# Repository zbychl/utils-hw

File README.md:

# utils-hw
Hardware utilities projects

## stlink-v2-clone-to-cortex-dbg-etm-adapter
Project for simple adapter allowing to attach STLink v2 Clone to the
20-Pin Cortex Debug + ETM Connector for ARM MCUs.

### STLink v2 clone
> **WARNING**: Be careful, there is a two different STLink v2 clone pinout version: http://blog.linuxbits.io/wp-content/uploads/2016/02/P1160461_clipped.jpg

This adapter is supports the following pinout

|          |            |
|----------|------------|
| RST  - 1 | 2  - SWCLK |
| GND  - 3 | 4  - SWDIO |
| SWIM - 5 | 6  - GND   |
| 3.3V - 7 | 8  - 3.3V  |
| 5.0V - 9 | 10 - 5.0V  |

### ARM MCU JTAG
http://www2.keil.com/coresight/coresight-connectors/

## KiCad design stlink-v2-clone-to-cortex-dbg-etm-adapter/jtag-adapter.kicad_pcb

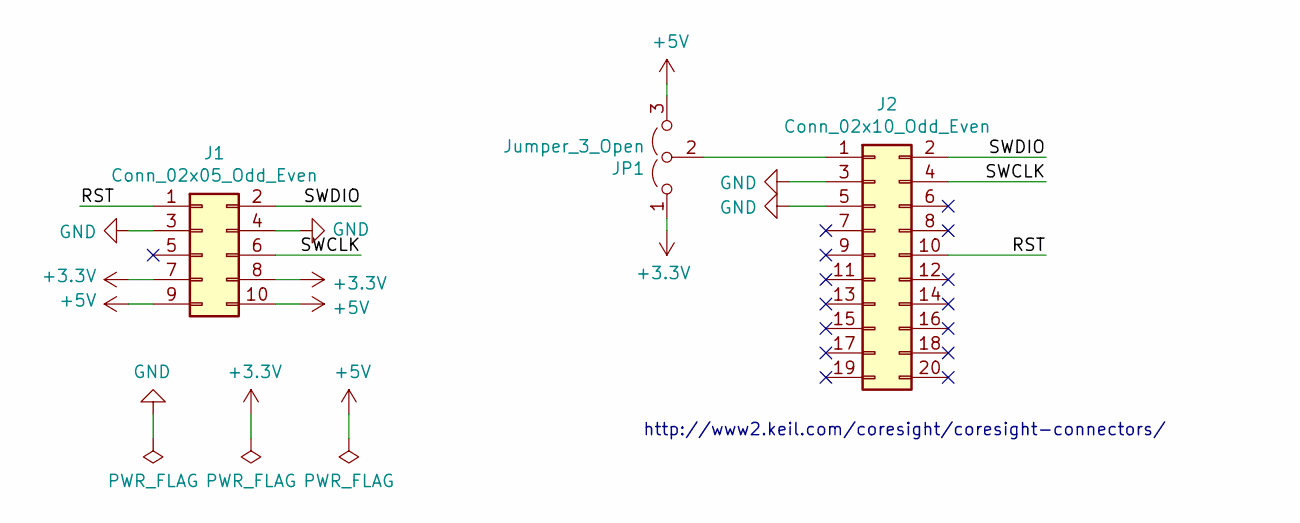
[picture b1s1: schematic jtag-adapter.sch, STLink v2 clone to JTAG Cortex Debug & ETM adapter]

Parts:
J1: Conn_02x05_Odd_Even; PinHeader_2x05_P2.54mm_Vertical_SMD
J2: Conn_02x10_Odd_Even; PinSocket_2x10_P1.27mm_Vertical_SMD
JP1: Jumper_3_Open; PinHeader_1x03_P1.27mm_Vertical

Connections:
+3V3: J1.7, J1.8, JP1.1 (A)
+5V: J1.9, J1.10, JP1.3 (B)
/RST: J1.1, J2.10
/SWCLK: J1.6, J2.4
/SWDIO: J1.2, J2.2
GND: J1.3, J1.4, J2.3, J2.5
unnamed: J2.1, JP1.2 (C)

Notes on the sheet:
http://www2.keil.com/coresight/coresight-connectors/

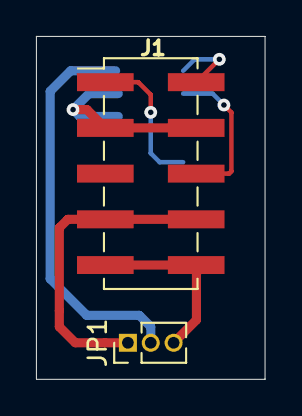
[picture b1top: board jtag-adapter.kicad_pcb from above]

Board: 2 copper layers, 12.7 x 19.1 mm, 3 parts (1 on the bottom side), 7 nets.

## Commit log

2020-08-02 [stlinkv2-jtagetm-adapter] Initial design.
2020-08-08 [stlinkv2-jtagetm-adapter] Change header to socket for 20pin connector. Update README.
2020-08-10 [stlinkv2-jtagetm-adapter] Add edge cuts to gerbers generation.
